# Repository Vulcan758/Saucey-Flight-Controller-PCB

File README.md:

# Saucey-Flight-Controller-PCB
This is a design repository for an ESP32 based flight controller (FC), "Saucey", that I made. 

## Technical Specifications
The FC uses an ESP32 S3 WROOM 1 module as the micrcontroller (MCU). It contains a 3.3 volt linear regulator (AMS1117 was used here) to power the MCU and the inertial measurement unit (IMU). The IMU used here is a MPU6050. This board is to be programmed through USB C. There is no onboard USB-Serial converter chip (such as CH2102) as ESP32 S3 can be programmed directly with its built USB-Serial converter on pins 18 and 19. A status LED is also availiable on board for testing and debugging. The FC board has 4 half bridge SI2306 logic level MOSFETs meant to drive coreless motors via JST connectors. This can however drive/ignite model rocket motors, LEDs and other low voltage output devices.

The goal of this project was to design a smart flight controller board with a credit card size form factor.

## PCB Schematic

## PCB Layout

### Top Layer

With ground pour

Without ground pour

### Bottom Layer

With ground pour

Without ground pour

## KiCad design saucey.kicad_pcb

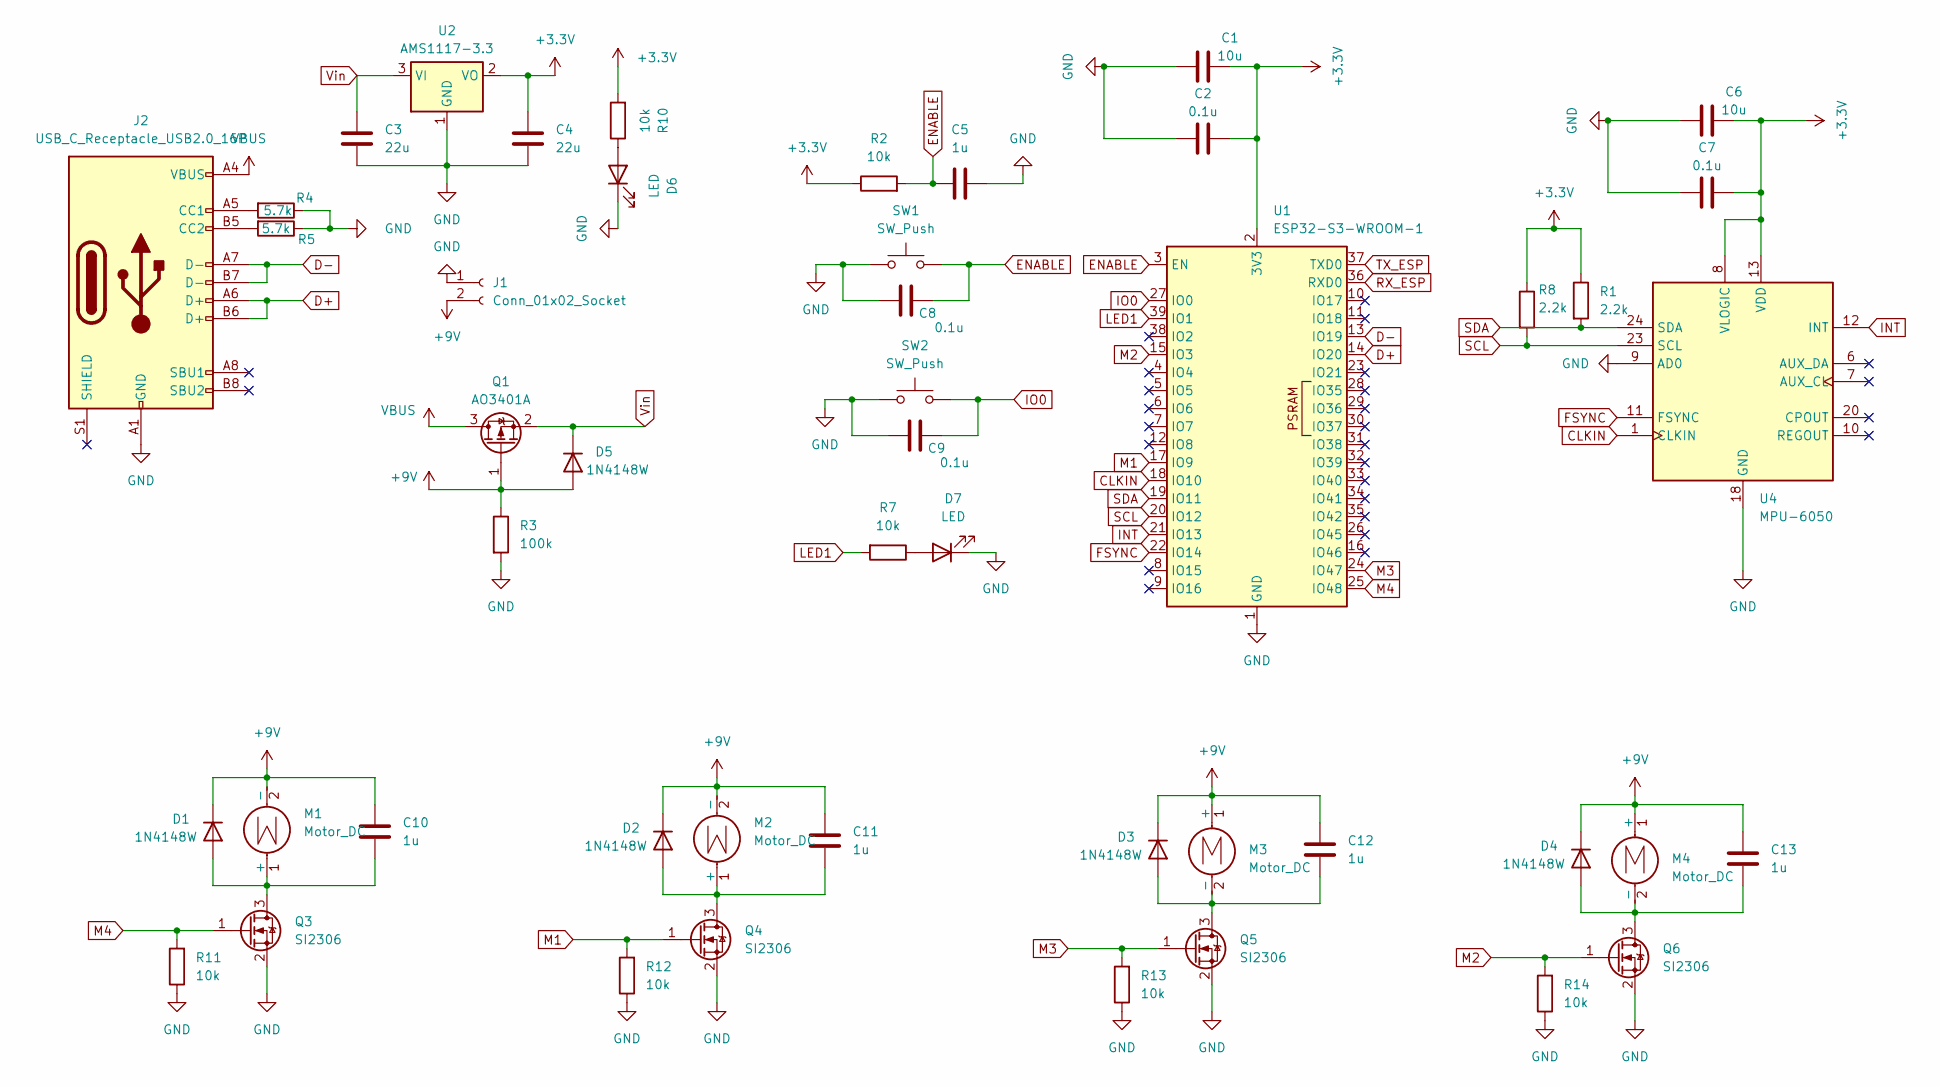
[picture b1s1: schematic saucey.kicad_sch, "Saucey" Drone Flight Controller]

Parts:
C1, C6: 10u; C_0603_1608Metric
C2, C7, C8, C9: 0.1u; C_0603_1608Metric
C3, C4: 22u; C_1210_3225Metric
C5, C10, C11, C12, C13: 1u; C_0402_1005Metric
D1, D2, D3, D4, D5: 1N4148W; D_SOD-123
D6, D7: LED; LED_0805_2012Metric_Pad1.15x1.40mm_HandSolder
J1: Conn_01x02_Socket; JST_XH_S2B-XH-A_1x02_P2.50mm_Horizontal
J2: USB_C_Receptacle_USB2.0_16P; USB_C_Receptacle_GCT_USB4105-xx-A_16P_TopMnt_Horizontal
M1, M2, M3, M4: Motor_DC; JST_XH_S2B-XH-A_1x02_P2.50mm_Horizontal
Q1: AO3401A; SOT-23
Q3, Q4, Q5, Q6: SI2306; SOT-23
R1, R8: 2.2k; R_0805_2012Metric
R2, R7, R10, R11, R12, R13, R14: 10k; R_0805_2012Metric
R3: 100k; R_0603_1608Metric
R4, R5: 5.7k; R_0603_1608Metric
SW1, SW2: SW_Push; SW_SPST_B3U-1000P
U1: ESP32-S3-WROOM-1
U2: AMS1117-3.3; SOT-223-3_TabPin2
U4: MPU-6050; InvenSense_QFN-24_4x4mm_P0.5mm

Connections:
+3.3V: C1.1, C2.1, C4.1, C6.1, C7.1, R1.1, R2.1, R8.1, R10.2, U1.2 (3V3), U2.2 (VO), U4.8 (VLOGIC), U4.13 (VDD)
+9V: C10.1, C11.1, C12.1, C13.1, D1.1 (K), D2.1 (K), D3.1 (K), D4.1 (K), D5.2 (A), J1.2, M1.2 (-), M2.2 (-), M3.1 (+), M4.1 (+), Q1.1 (G), R3.1
CLKIN: U1.18 (IO10), U4.1 (CLKIN)
D+: J2.A6 (D+), J2.B6 (D+), U1.14 (IO20)
D-: J2.A7 (D-), J2.B7 (D-), U1.13 (IO19)
ENABLE: C5.2, C8.1, R2.2, SW1.2, U1.3 (EN)
FSYNC: U1.22 (IO14), U4.11 (FSYNC)
GND: C1.2, C2.2, C3.2, C4.2, C5.1, C6.2, C7.2, C8.2, C9.2, D6.1 (K), D7.1 (K), J1.1, J2.A1 (GND), J2.A12 (GND), J2.B1 (GND), J2.B12 (GND), Q3.2 (S), Q4.2 (S), Q5.2 (S), Q6.2 (S), R3.2, R4.1, R5.1, R11.1, R12.1, R13.1, R14.1, SW1.1, SW2.1, U1.1 (GND), U1.40 (GND), U1.41 (GND), U2.1 (GND), U4.9 (AD0), U4.18 (GND)
INT: U1.21 (IO13), U4.12 (INT)
IO0: C9.1, SW2.2, U1.27 (IO0)
LED1: R7.2, U1.39 (IO1)
M1: Q4.1 (G), R12.2, U1.17 (IO9)
M2: Q6.1 (G), R14.2, U1.15 (IO3)
M3: Q5.1 (G), R13.2, U1.24 (IO47)
M4: Q3.1 (G), R11.2, U1.25 (IO48)
unnamed: C10.2, D1.2 (A), M1.1 (+), Q3.3 (D)
unnamed: C11.2, D2.2 (A), M2.1 (+), Q4.3 (D)
unnamed: C12.2, D3.2 (A), M3.2 (-), Q5.3 (D)
unnamed: C13.2, D4.2 (A), M4.2 (-), Q6.3 (D)
unnamed: D6.2 (A), R10.1
unnamed: D7.2 (A), R7.1
unnamed: J2.A5 (CC1), R4.2
unnamed: J2.B5 (CC2), R5.2
RX_ESP: U1.36 (RXD0)
SCL: R8.2, U1.20 (IO12), U4.23 (SCL)
SDA: R1.2, U1.19 (IO11), U4.24 (SDA)
TX_ESP: U1.37 (TXD0)
VBUS: J2.A4 (VBUS), J2.A9 (VBUS), J2.B4 (VBUS), J2.B9 (VBUS), Q1.3 (D)
Vin: C3.1, D5.1 (K), Q1.2 (S), U2.3 (VI)

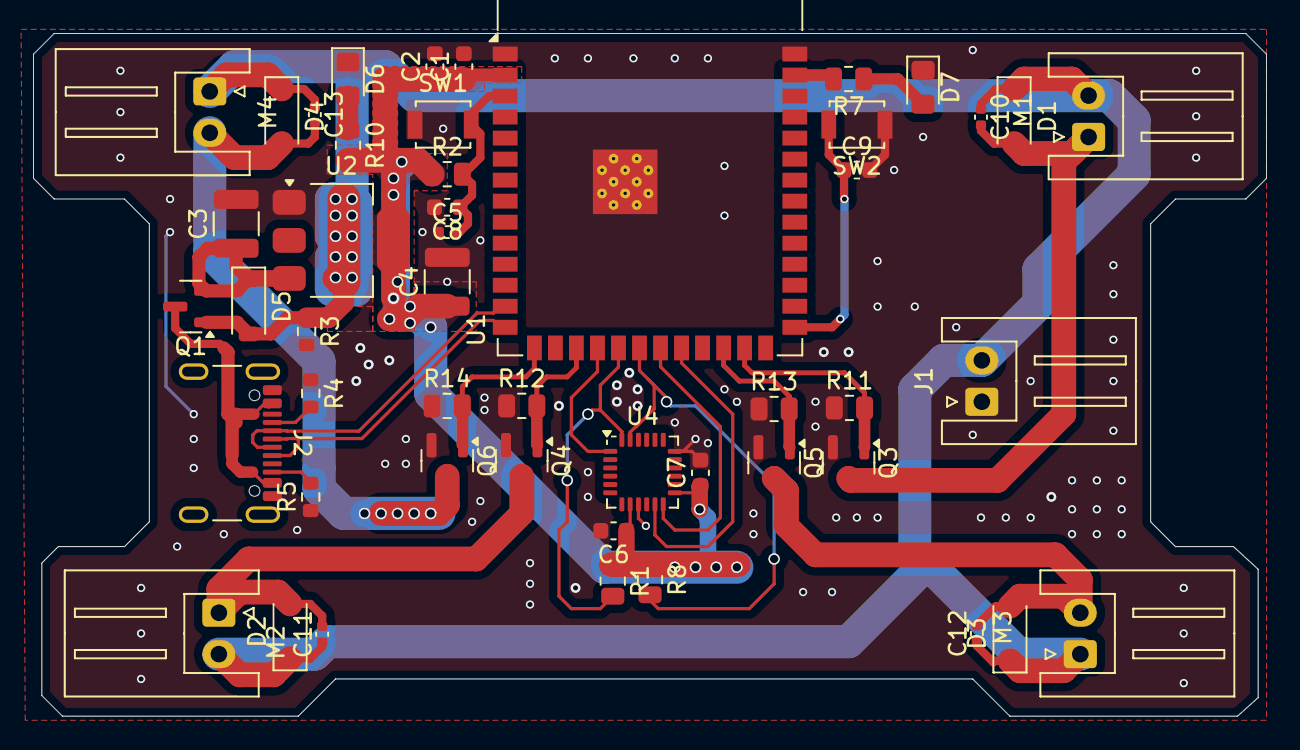
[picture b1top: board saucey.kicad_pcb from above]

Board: 2 copper layers, 74.5 x 41.2 mm, 48 parts (0 on the bottom side), 27 nets.

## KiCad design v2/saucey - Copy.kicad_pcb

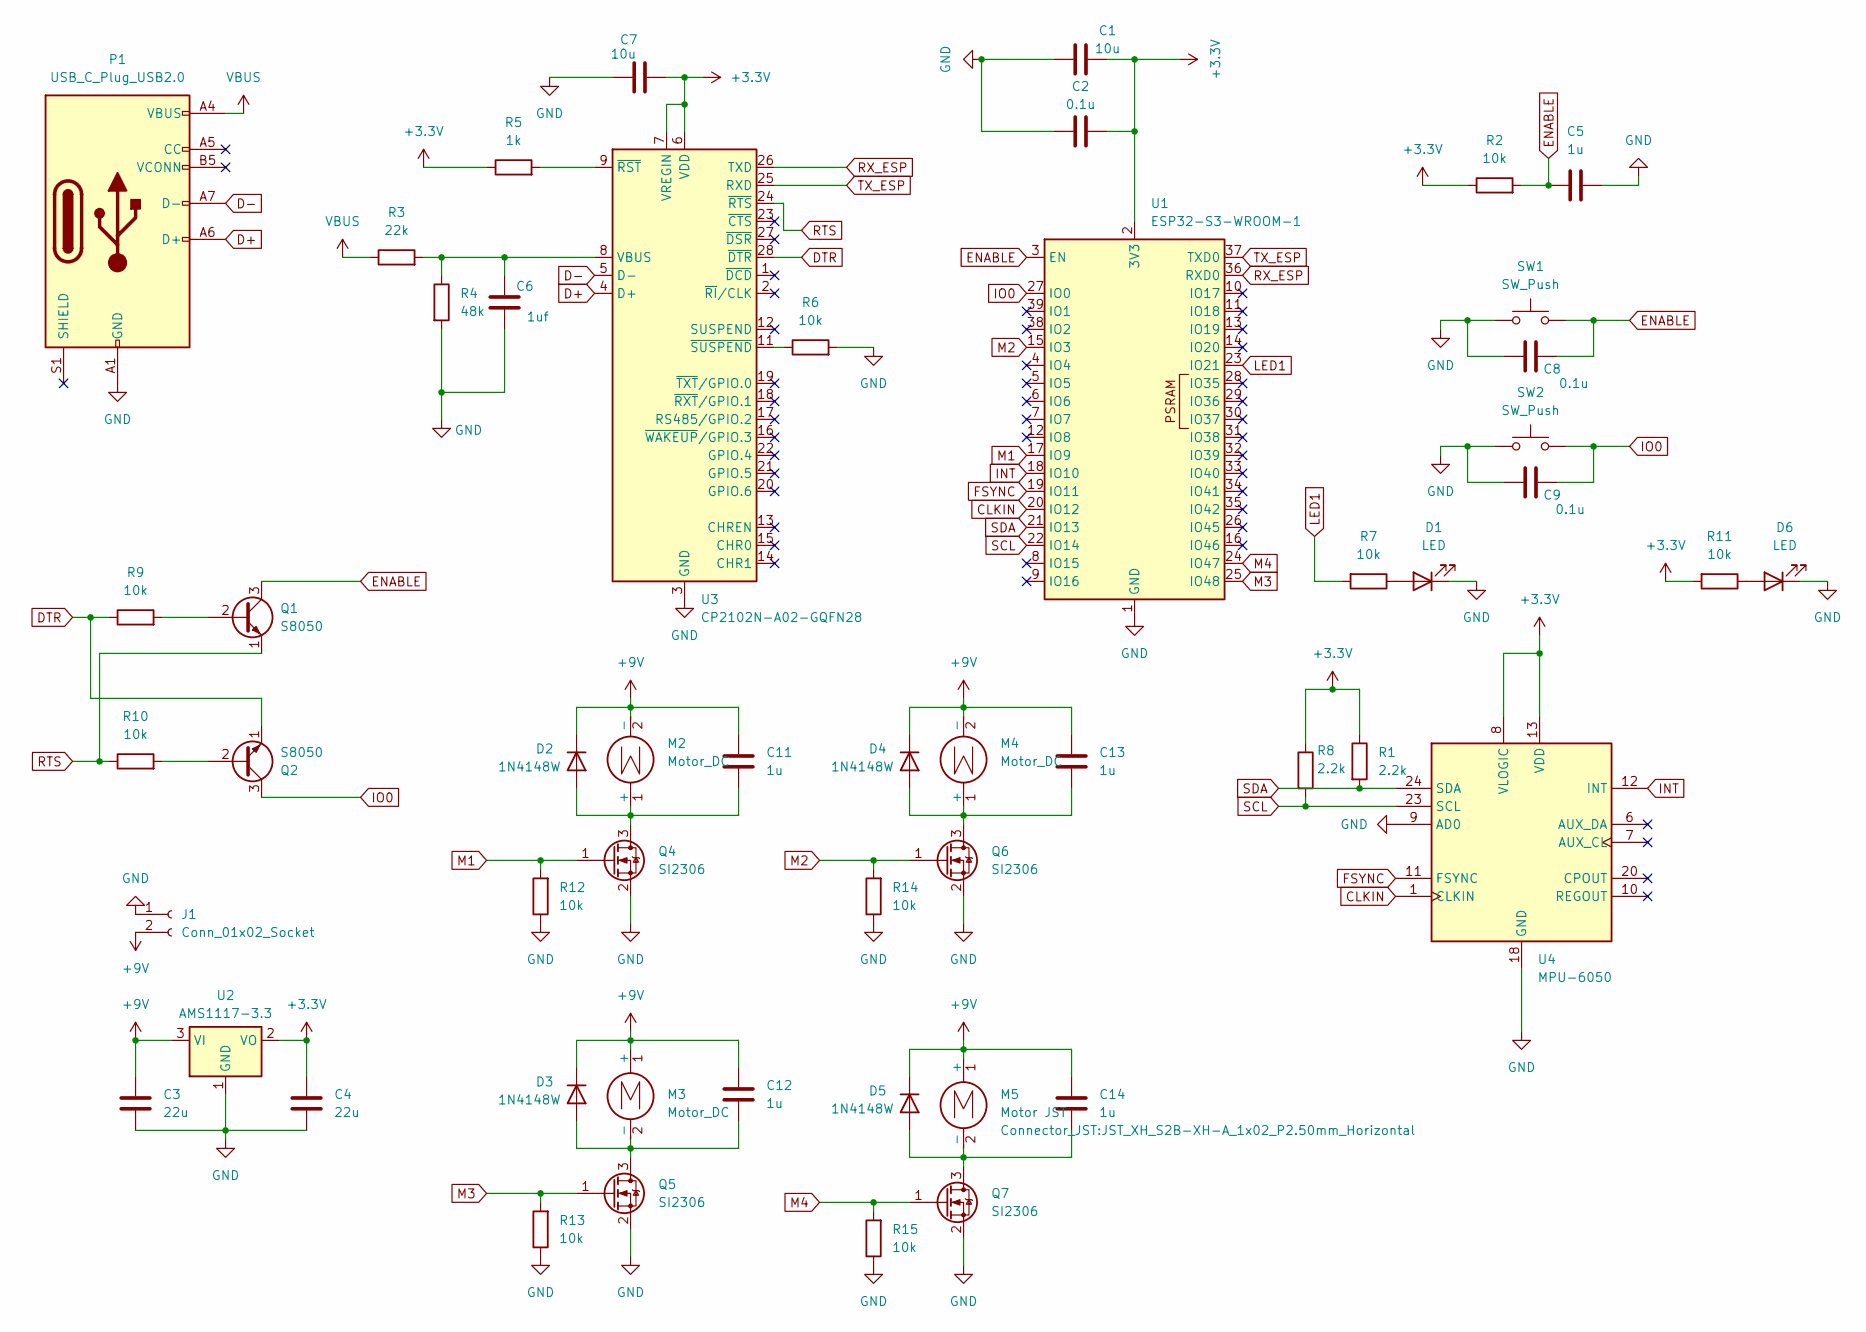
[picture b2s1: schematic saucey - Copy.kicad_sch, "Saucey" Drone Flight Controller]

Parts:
C1, C7: 10u; C_0603_1608Metric
C2, C8, C9: 0.1u; C_0603_1608Metric
C3, C4: 22u; C_1210_3225Metric
C5, C11, C12, C13, C14: 1u; C_0402_1005Metric
C6: 1uf; C_0402_1005Metric
D1, D6: LED; LED_0805_2012Metric_Pad1.15x1.40mm_HandSolder
D2, D3, D4, D5: 1N4148W; D_SOD-123
J1: Conn_01x02_Socket; JST_XH_S2B-XH-A_1x02_P2.50mm_Horizontal
M2, M3, M4: Motor_DC; JST_XH_S2B-XH-A_1x02_P2.50mm_Horizontal
M5: Motor JST; JST_XH_S2B-XH-A_1x02_P2.50mm_Horizontal
P1: USB_C_Plug_USB2.0; USB_C_Receptacle_GCT_USB4105-xx-A_16P_TopMnt_Horizontal
Q1, Q2: S8050; TO-92_Inline
Q4, Q5, Q6, Q7: SI2306; SOT-23
R1, R8: 2.2k; R_0805_2012Metric
R2, R6, R7, R9, R10, R11, R12, R13, R14, R15: 10k; R_0805_2012Metric
R3: 22k; R_1210_3225Metric
R4: 48k; R_1206_3216Metric
R5: 1k; R_1206_3216Metric
SW1, SW2: SW_Push; SW_SPST_B3U-1000P
U1: ESP32-S3-WROOM-1
U2: AMS1117-3.3; SOT-223-3_TabPin2
U3: CP2102N-A02-GQFN28; QFN-28-1EP_5x5mm_P0.5mm_EP3.35x3.35mm
U4: MPU-6050; InvenSense_QFN-24_4x4mm_P0.5mm

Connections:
+3.3V: C1.1, C2.1, C4.1, C7.1, R1.1, R2.1, R5.1, R8.1, R11.2, U1.2 (3V3), U2.2 (VO), U3.6 (VDD), U3.7 (VREGIN), U4.8 (VLOGIC), U4.13 (VDD)
+9V: C3.1, C11.1, C12.1, C13.1, C14.1, D2.1 (K), D3.1 (K), D4.1 (K), D5.1 (K), J1.2, M2.2 (-), M3.1 (+), M4.2 (-), M5.1 (+), U2.3 (VI)
CLKIN: U1.20 (IO12), U4.1 (CLKIN)
D+: P1.A6 (D+), U3.4 (D+)
D-: P1.A7 (D-), U3.5 (D-)
DTR: Q2.1 (E), R9.1, U3.28 (~DTR)
ENABLE: C5.2, C8.1, Q1.3 (C), R2.2, SW1.2, U1.3 (EN)
FSYNC: U1.19 (IO11), U4.11 (FSYNC)
GND: C1.2, C2.2, C3.2, C4.2, C5.1, C6.2, C7.2, C8.2, C9.2, D1.1 (K), D6.1 (K), J1.1, P1.A1 (GND), P1.A12 (GND), P1.B1 (GND), P1.B12 (GND), Q4.2 (S), Q5.2 (S), Q6.2 (S), Q7.2 (S), R4.2, R6.2, R12.1, R13.1, R14.1, R15.1, SW1.1, SW2.1, U1.1 (GND), U1.40 (GND), U1.41 (GND), U2.1 (GND), U3.3 (GND), U3.29 (GND), U4.9 (AD0), U4.18 (GND)
INT: U1.18 (IO10), U4.12 (INT)
IO0: C9.1, Q2.3 (C), SW2.2, U1.27 (IO0)
LED1: R7.2, U1.23 (IO21)
M1: Q4.1 (G), R12.2, U1.17 (IO9)
M2: Q6.1 (G), R14.2, U1.15 (IO3)
M3: Q5.1 (G), R13.2, U1.25 (IO48)
M4: Q7.1 (G), R15.2, U1.24 (IO47)
unnamed: D1.2 (A), R7.1
unnamed: C11.2, D2.2 (A), M2.1 (+), Q4.3 (D)
unnamed: C12.2, D3.2 (A), M3.2 (-), Q5.3 (D)
unnamed: C13.2, D4.2 (A), M4.1 (+), Q6.3 (D)
unnamed: C14.2, D5.2 (A), M5.2 (-), Q7.3 (D)
unnamed: D6.2 (A), R11.1
unnamed: Q1.2 (B), R9.2
unnamed: Q2.2 (B), R10.2
unnamed: C6.1, R3.2, R4.1, U3.8 (VBUS)
unnamed: R5.2, U3.9 (~RST)
unnamed: R6.1, U3.11 (~SUSPEND)
RTS: Q1.1 (E), R10.1, U3.24 (~RTS)
RX_ESP: U1.36 (RXD0), U3.26 (TXD)
SCL: R8.2, U1.22 (IO14), U4.23 (SCL)
SDA: R1.2, U1.21 (IO13), U4.24 (SDA)
TX_ESP: U1.37 (TXD0), U3.25 (RXD)
VBUS: P1.A4 (VBUS), P1.A9 (VBUS), P1.B4 (VBUS), P1.B9 (VBUS), R3.1

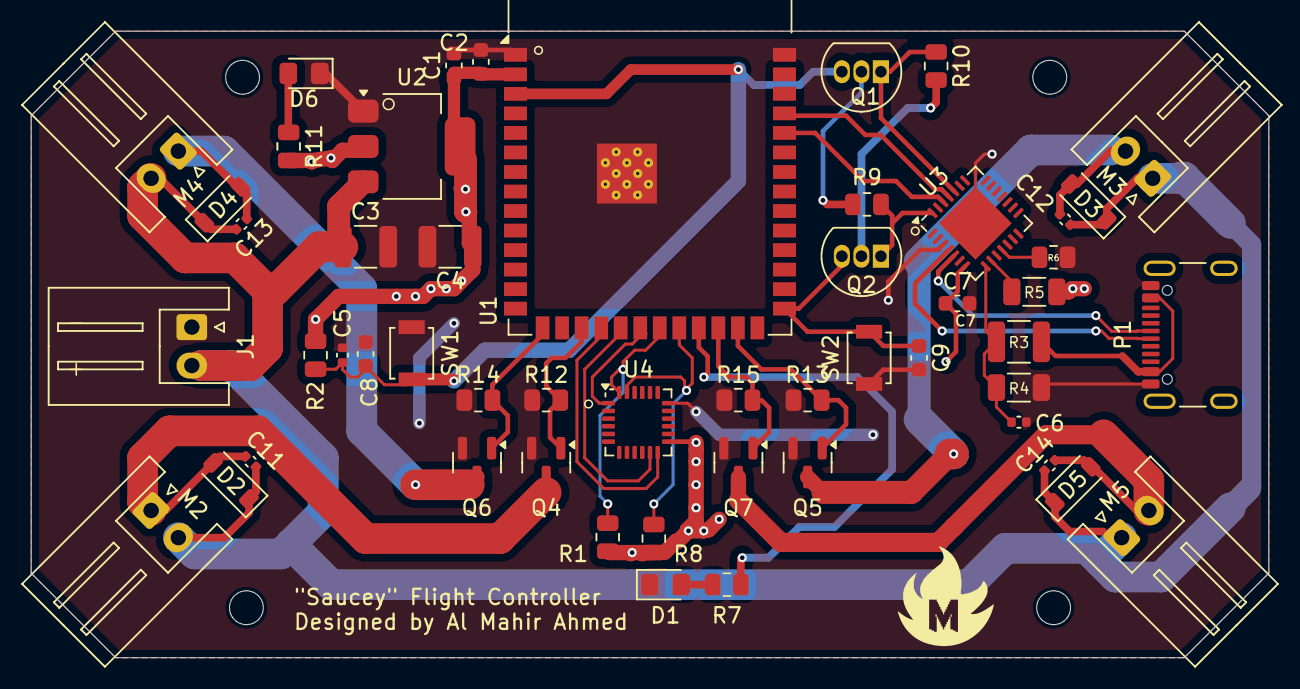
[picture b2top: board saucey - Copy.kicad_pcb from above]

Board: 2 copper layers, 80.5 x 40.8 mm, 52 parts (0 on the bottom side), 33 nets.

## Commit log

2024-10-22 Flight controller details
2024-10-22 added schematic and pcb layout
